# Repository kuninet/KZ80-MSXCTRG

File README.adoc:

== KZ80シリーズ MSX カートリッジスロットボード

=== 概要
* SBC8080バスなどに接続する MSX ROMカセット カートリッジスロットボードですです。試作段階です。

=== 注意
* KZ80-CPUB REV3 のZ80専用信号線バスと、KZ80-IOB REV2以降(アドレスデコードの関係で...)のAポートを使用します。またメモリーボードKZ80-1MSRAMのパターンカット等の改造が必要です。

=== ライセンス
* 本プロジェクトのデータはMITライセンスのもとで公開します。

=== 参考
* http://ngs.no.coocan.jp/doc/wiki.cgi/datapack?page=7%BE%CF+MSX2%2B%B2%F3%CF%A9%CE%E3

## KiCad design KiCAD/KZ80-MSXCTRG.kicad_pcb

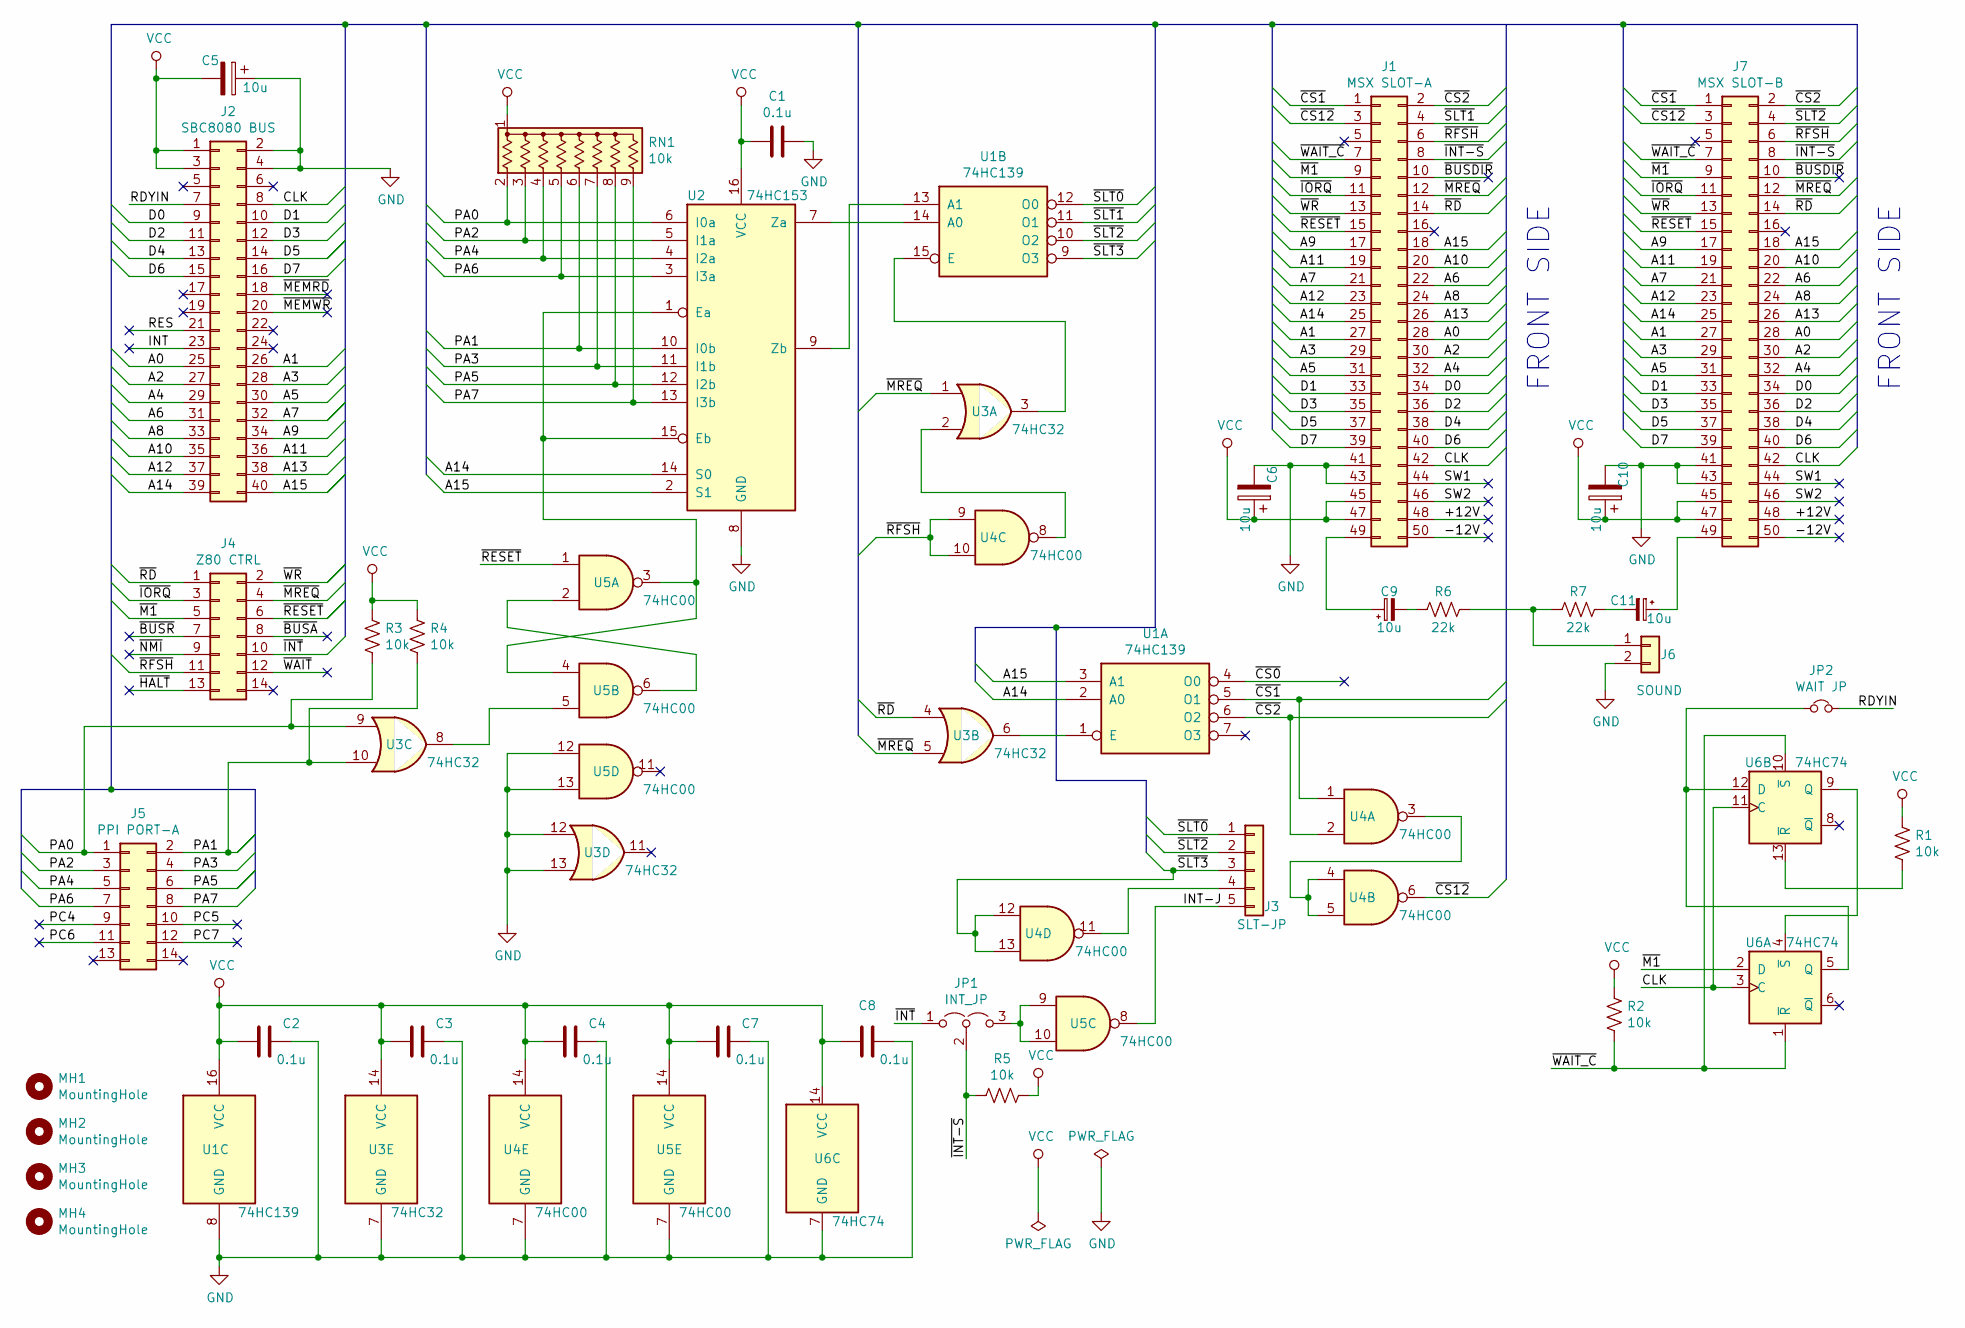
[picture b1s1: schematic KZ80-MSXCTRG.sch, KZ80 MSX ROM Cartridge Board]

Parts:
C1, C2, C3, C4, C7, C8: 0.1u; C_Disc_D3.0mm_W1.6mm_P2.50mm
C5, C6, C9, C10, C11: 10u; CP_Radial_D5.0mm_P2.50mm
J1: MSX SLOT-A; PCB_Edge_Conn_2x25_P2.54mm_Vertical
J2: SBC8080 BUS; PinHeader_2x20_P2.54mm_Horizontal
J3: SLT-JP; PinHeader_1x05_P2.54mm_Horizontal
J4: Z80 CTRL; PinHeader_2x07_P2.54mm_Vertical
J5: PPI PORT-A; PinHeader_2x07_P2.54mm_Vertical
J6: SOUND; PinHeader_1x02_P2.54mm_Horizontal
J7: MSX SLOT-B; PCB_Edge_Conn_2x25_P2.54mm_Vertical
JP1: INT_JP; PinHeader_1x03_P2.54mm_Vertical
JP2: WAIT JP; PinHeader_1x02_P2.54mm_Vertical
MH1, MH2, MH3, MH4: MountingHole; MountingHole_3.2mm_M3
R1, R2, R3, R4, R5: 10k; R_Axial_DIN0207_L6.3mm_D2.5mm_P10.16mm_Horizontal
R6, R7: 22k; R_Axial_DIN0207_L6.3mm_D2.5mm_P10.16mm_Horizontal
RN1: 10k; R_Array_SIP9
U1: 74HC139; DIP-16_W7.62mm_Socket
U2: 74HC153; DIP-16_W7.62mm_Socket
U3: 74HC32; DIP-14_W7.62mm_Socket
U4, U5: 74HC00; DIP-14_W7.62mm_Socket
U6: 74HC74; DIP-14_W7.62mm_Socket

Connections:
/+12V: J1.48, J7.48
/-12V: J1.50, J7.50
/A0: J1.28, J2.25, J7.28
/A1: J1.27, J2.26, J7.27
/A2: J1.30, J2.27, J7.30
/A3: J1.29, J2.28, J7.29
/A4: J1.32, J2.29, J7.32
/A5: J1.31, J2.30, J7.31
/A6: J1.22, J2.31, J7.22
/A7: J1.21, J2.32, J7.21
/A8: J1.24, J2.33, J7.24
/A9: J1.17, J2.34, J7.17
/A10: J1.20, J2.35, J7.20
/A11: J1.19, J2.36, J7.19
/A12: J1.23, J2.37, J7.23
/A13: J1.26, J2.38, J7.26
/A14: J1.25, J2.39, J7.25, U1.2 (A0), U2.14 (S0)
/A15: J1.18, J2.40, J7.18, U1.3 (A1), U2.2 (S1)
/CLK: J1.42, J2.8, J7.42, U6.3 (C), U6.11 (C)
/D0: J1.34, J2.9, J7.34
/D1: J1.33, J2.10, J7.33
/D2: J1.36, J2.11, J7.36
/D3: J1.35, J2.12, J7.35
/D4: J1.38, J2.13, J7.38
/D5: J1.37, J2.14, J7.37
/D6: J1.40, J2.15, J7.40
/D7: J1.39, J2.16, J7.39
/INT: J2.23
/INT-J: J3.5, U5.8
/PA0: J5.1, R3.2, RN1.2 (R1), U2.6 (I0a), U3.9
/PA1: J5.2, R4.2, RN1.6 (R5), U2.10 (I0b), U3.10
/PA2: J5.3, RN1.3 (R2), U2.5 (I1a)
/PA3: J5.4, RN1.7 (R6), U2.11 (I1b)
/PA4: J5.5, RN1.4 (R3), U2.4 (I2a)
/PA5: J5.6, RN1.8 (R7), U2.12 (I2b)
/PA6: J5.7, RN1.5 (R4), U2.3 (I3a)
/PA7: J5.8, RN1.9 (R8), U2.13 (I3b)
/PC4: J5.9
/PC5: J5.10
/PC6: J5.11
/PC7: J5.12
/RDYIN: J2.7, JP2.2
/RES: J2.21
/SW1: J1.44, J7.44
/SW2: J1.46, J7.46
/~BUSA: J4.8
/~BUSDIR: J1.10, J7.10
/~BUSR: J4.7
/~CS0: U1.4 (O0)
/~CS1: J1.1, J7.1, U1.5 (O1), U4.1
/~CS2: J1.2, J7.2, U1.6 (O2), U4.2
/~CS12: J1.3, J7.3, U4.6
/~HALT: J4.13
/~INT: J4.10, JP1.1 (A)
/~INT-S: J1.8, J7.8, JP1.2 (C), R5.2
/~IORQ: J1.11, J4.3, J7.11
/~M1: J1.9, J4.5, J7.9, U6.2 (D)
/~MEMRD: J2.18
/~MEMWR: J2.20
/~MREQ: J1.12, J4.4, J7.12, U3.1, U3.5
/~NMI: J4.9
/~RD: J1.14, J4.1, J7.14, U3.4
/~RESET: J1.15, J4.6, J7.15, U5.1
/~RFSH: J1.6, J4.11, J7.6, U4.9, U4.10
/~SLT0: J3.1, U1.12 (O0)
/~SLT1: J1.4, U1.11 (O1)
/~SLT2: J3.2, J7.4, U1.10 (O2)
/~SLT3: J3.3, U1.9 (O3), U4.12, U4.13
/~WAIT: J4.12
/~WAIT_C: J1.7, J7.7, R2.2, U6.1 (~R), U6.10 (~S)
/~WR: J1.13, J4.2, J7.13
GND: C1.1, C2.1, C3.1, C4.1, C5.1, C6.2, C7.1, C8.1, C10.2, J1.41, J1.43, J2.2, J2.4, J6.2, J7.41, J7.43, U1.8 (GND), U2.8 (GND), U3.7 (GND), U3.12, U3.13, U4.7 (GND), U5.7 (GND), U5.12, U5.13, U6.7 (GND)
unnamed: C9.1, J1.49
unnamed: C9.2, R6.2
unnamed: C11.1, J7.49
unnamed: C11.2, R7.1
unnamed: J3.4, U4.11
unnamed: J6.1, R6.1, R7.2
unnamed: JP1.3 (B), U5.9, U5.10
unnamed: JP2.1, U6.5 (Q), U6.12 (D)
unnamed: R1.2, U6.13 (~R)
unnamed: U1.1 (E), U3.6
unnamed: U1.13 (A1), U2.9 (Zb)
unnamed: U1.14 (A0), U2.7 (Za)
unnamed: U1.15 (E), U3.3
unnamed: U2.1 (Ea), U2.15 (Eb), U5.3, U5.4
unnamed: U3.2, U4.8
unnamed: U3.8, U5.5
unnamed: U4.3, U4.4, U4.5
unnamed: U5.2, U5.6
unnamed: U6.4 (~S), U6.9 (Q)
VCC: C1.2, C2.2, C3.2, C4.2, C5.2, C6.1, C7.2, C8.2, C10.1, J1.45, J1.47, J2.1, J2.3, J7.45, J7.47, R1.1, R2.1, R3.1, R4.1, R5.1, RN1.1 (common), U1.16 (VCC), U2.16 (VCC), U3.14 (VCC), U4.14 (VCC), U5.14 (VCC), U6.14 (VCC)

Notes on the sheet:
FRONT SIDE

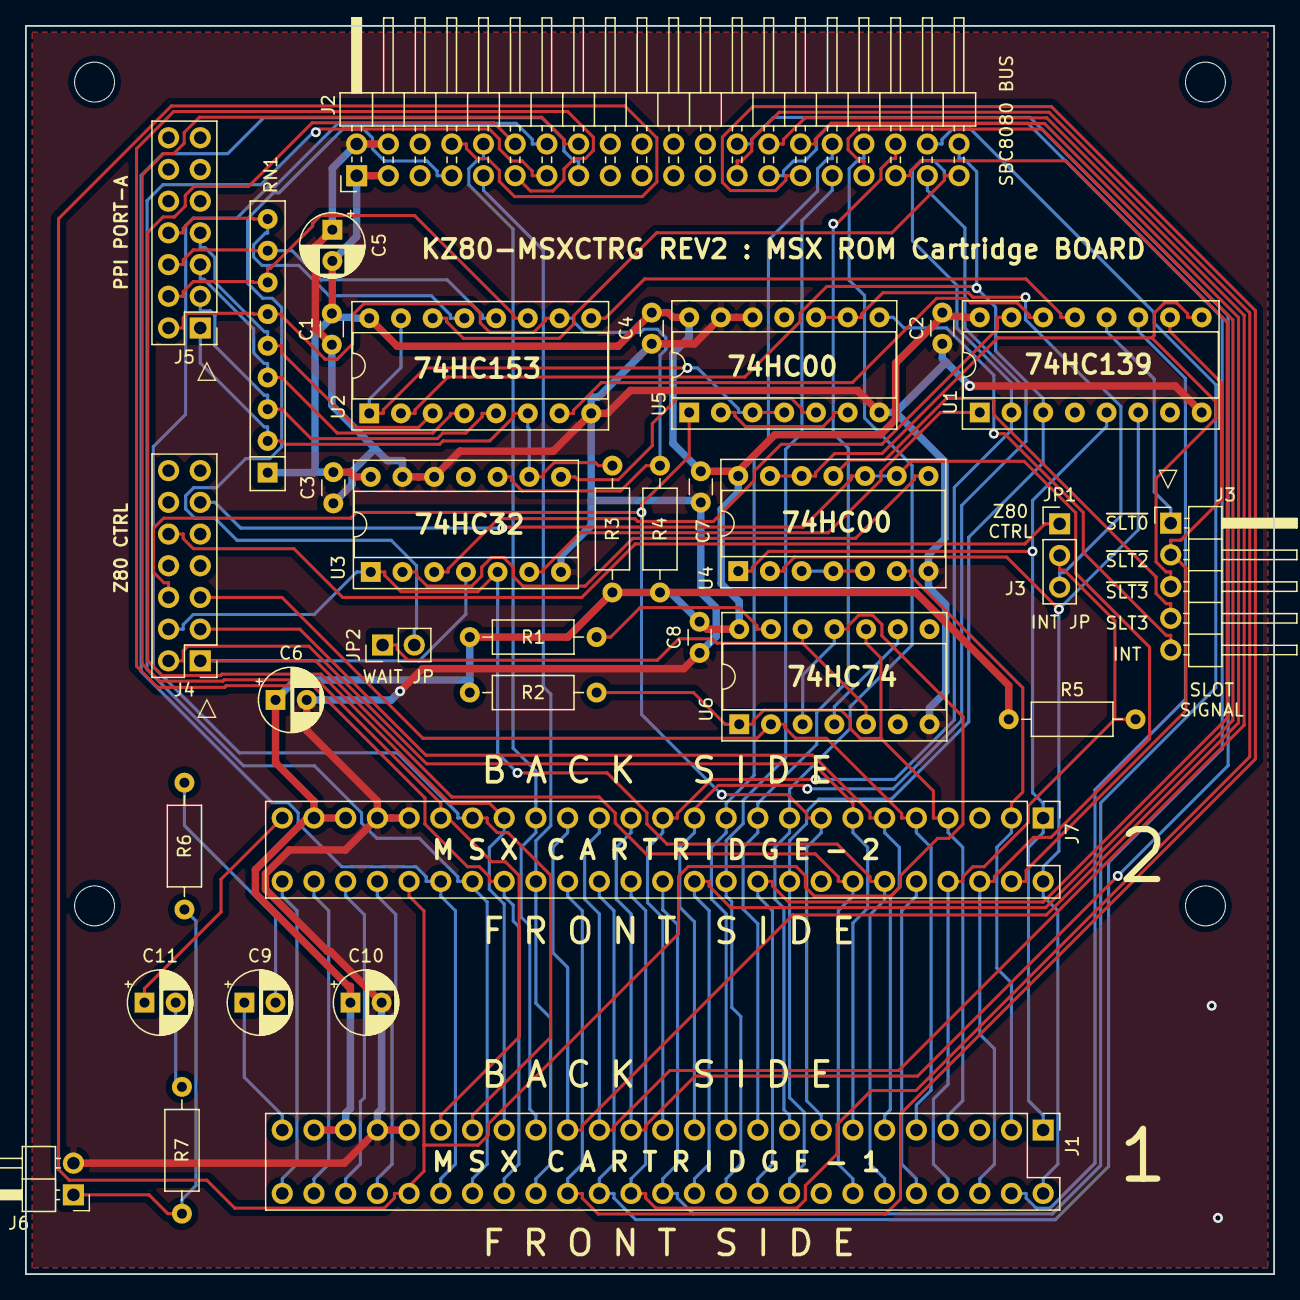
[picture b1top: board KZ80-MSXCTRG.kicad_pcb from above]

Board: 2 copper layers, 100.0 x 100.0 mm, 38 parts (0 on the bottom side), 78 nets.

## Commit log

2019-09-22 初期コミット
2019-09-24 割り込み信号を外部端子と切り替えるジャンパ装備
2019-09-30 74HC153コントロールをPPI出力で暫定実施
2019-10-01 回路改良
2019-10-05 74HC153コントロール用RS-FF追加
2019-10-05 プリントパターン見直し
2019-12-21 REV1基板(1WAIT回路追加) ガーバーデータ出力
2019-12-21 REV1回路図面PDF/jpg差し替え
2021-02-08 2スロット対応
2021-02-08 パターン改良ぬ
2021-02-18 ガーバーデータ出力
2021-03-27 REV2回路図イメージ出力
